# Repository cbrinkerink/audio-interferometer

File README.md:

# audio-interferometer
Using an FPGA to sample audio from multiple digital microphones and perform correlation, then visualise it on a PC. Presently, this repository is a hodgepodge of things including source files, executables, libraries and build scripts. I have tried to stay cross-platform, but everything so far only has been made to compile on OSX.

## Sources used
I have used OpenGL C++ code from the LearnOpenGL tutorial series (specifically, tutorial 4.1 from section 1). I got the serial connection stuff from a question on stackoverflow :)

The Ethernet core is from LiteEth, it is an independently synthesized core using the gen.py script in that codebase.

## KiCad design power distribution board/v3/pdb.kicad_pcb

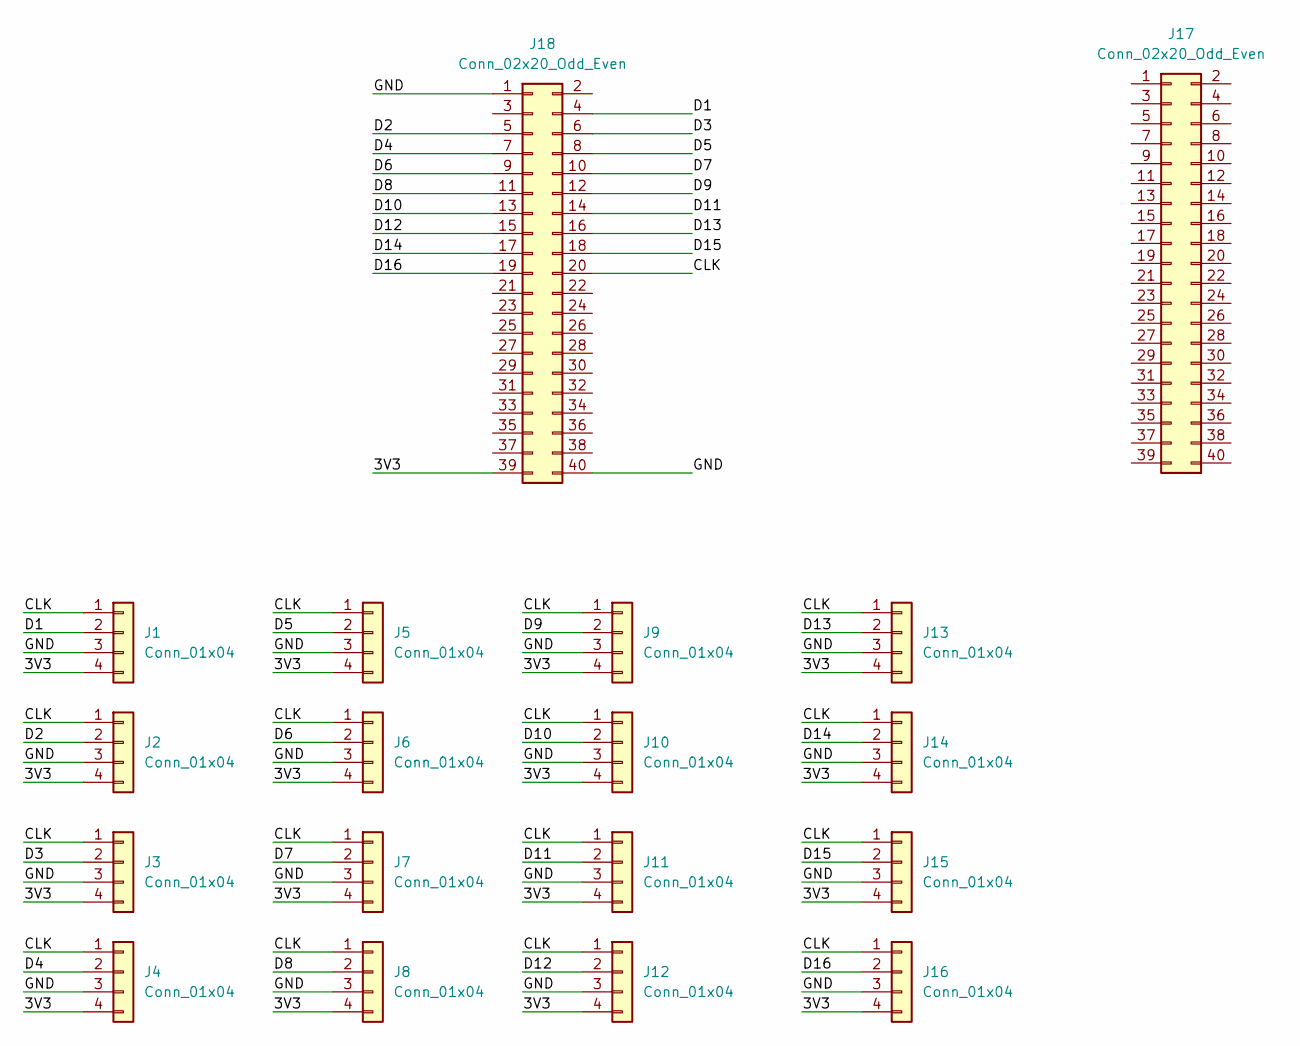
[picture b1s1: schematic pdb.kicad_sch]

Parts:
J1, J2, J3, J4, J5, J6, J7, J8, J9, J10, J11, J12, J13, J14, J15, J16: Conn_01x04; PinHeader_1x04_P2.54mm_Horizontal
J17, J18: Conn_02x20_Odd_Even; PinSocket_2x20_P2.54mm_Vertical

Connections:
/3V3: J1.4, J2.4, J3.4, J4.4, J5.4, J6.4, J7.4, J8.4, J9.4, J10.4, J11.4, J12.4, J13.4, J14.4, J15.4, J16.4, J18.39
/CLK: J1.1, J2.1, J3.1, J4.1, J5.1, J6.1, J7.1, J8.1, J9.1, J10.1, J11.1, J12.1, J13.1, J14.1, J15.1, J16.1, J18.20
/D1: J1.2, J18.4
/D2: J2.2, J18.5
/D3: J3.2, J18.6
/D4: J4.2, J18.7
/D5: J5.2, J18.8
/D6: J6.2, J18.9
/D7: J7.2, J18.10
/D8: J8.2, J18.11
/D9: J9.2, J18.12
/D10: J10.2, J18.13
/D11: J11.2, J18.14
/D12: J12.2, J18.15
/D13: J13.2, J18.16
/D14: J14.2, J18.17
/D15: J15.2, J18.18
/D16: J16.2, J18.19
/GND: J1.3, J2.3, J3.3, J4.3, J5.3, J6.3, J7.3, J8.3, J9.3, J10.3, J11.3, J12.3, J13.3, J14.3, J15.3, J16.3, J18.1, J18.40

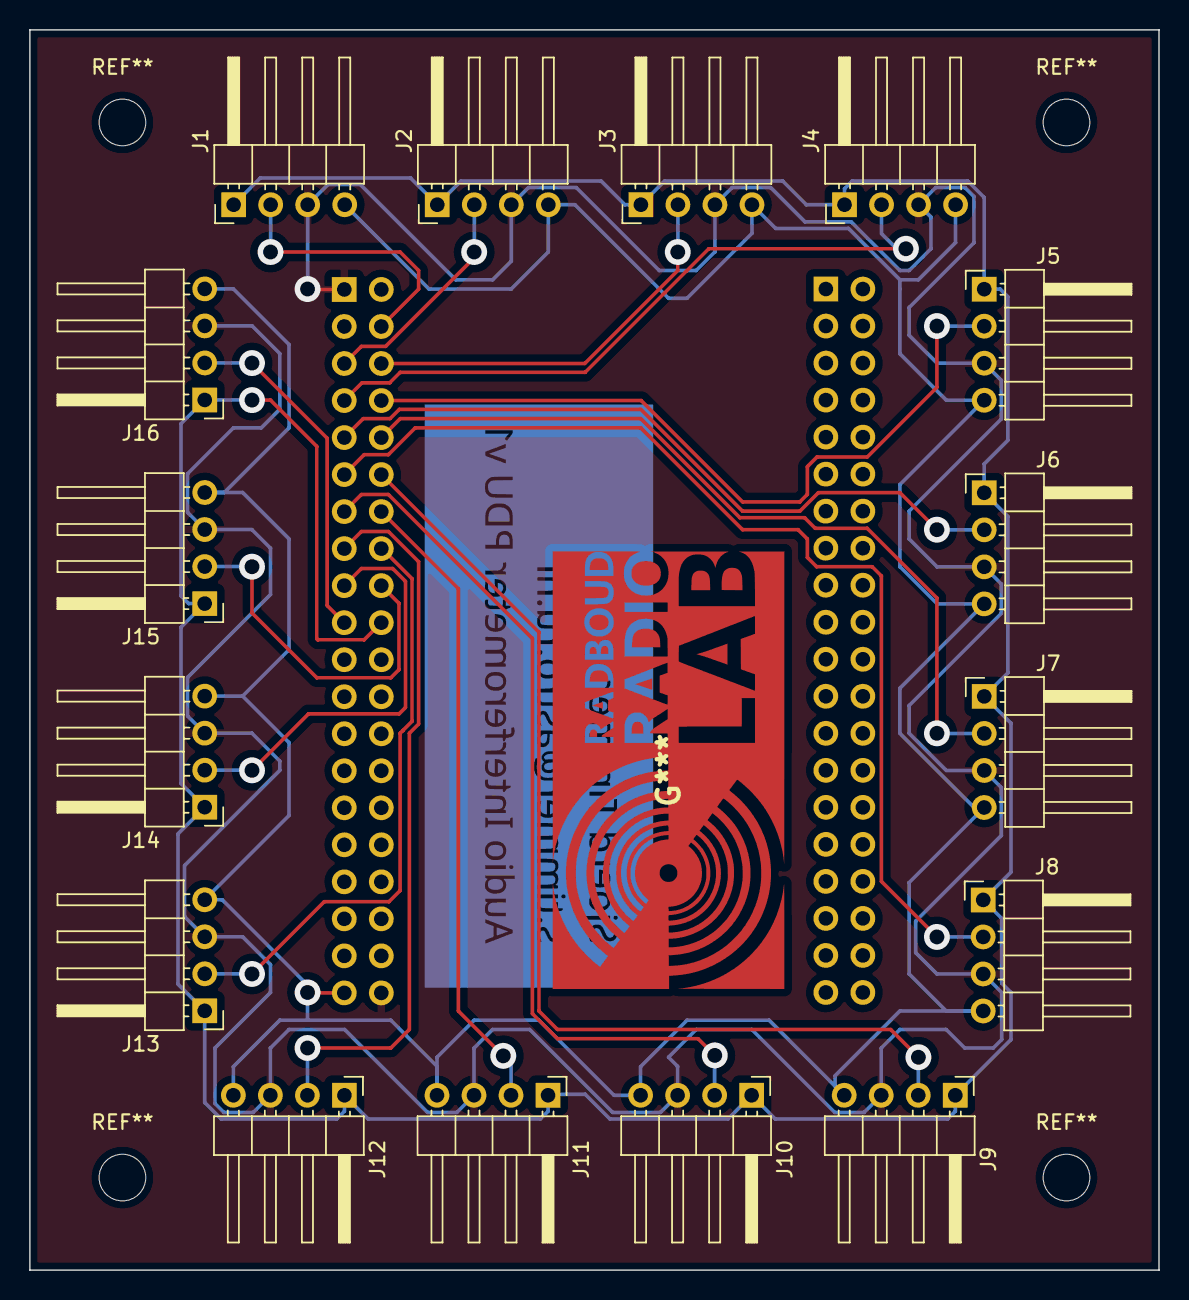
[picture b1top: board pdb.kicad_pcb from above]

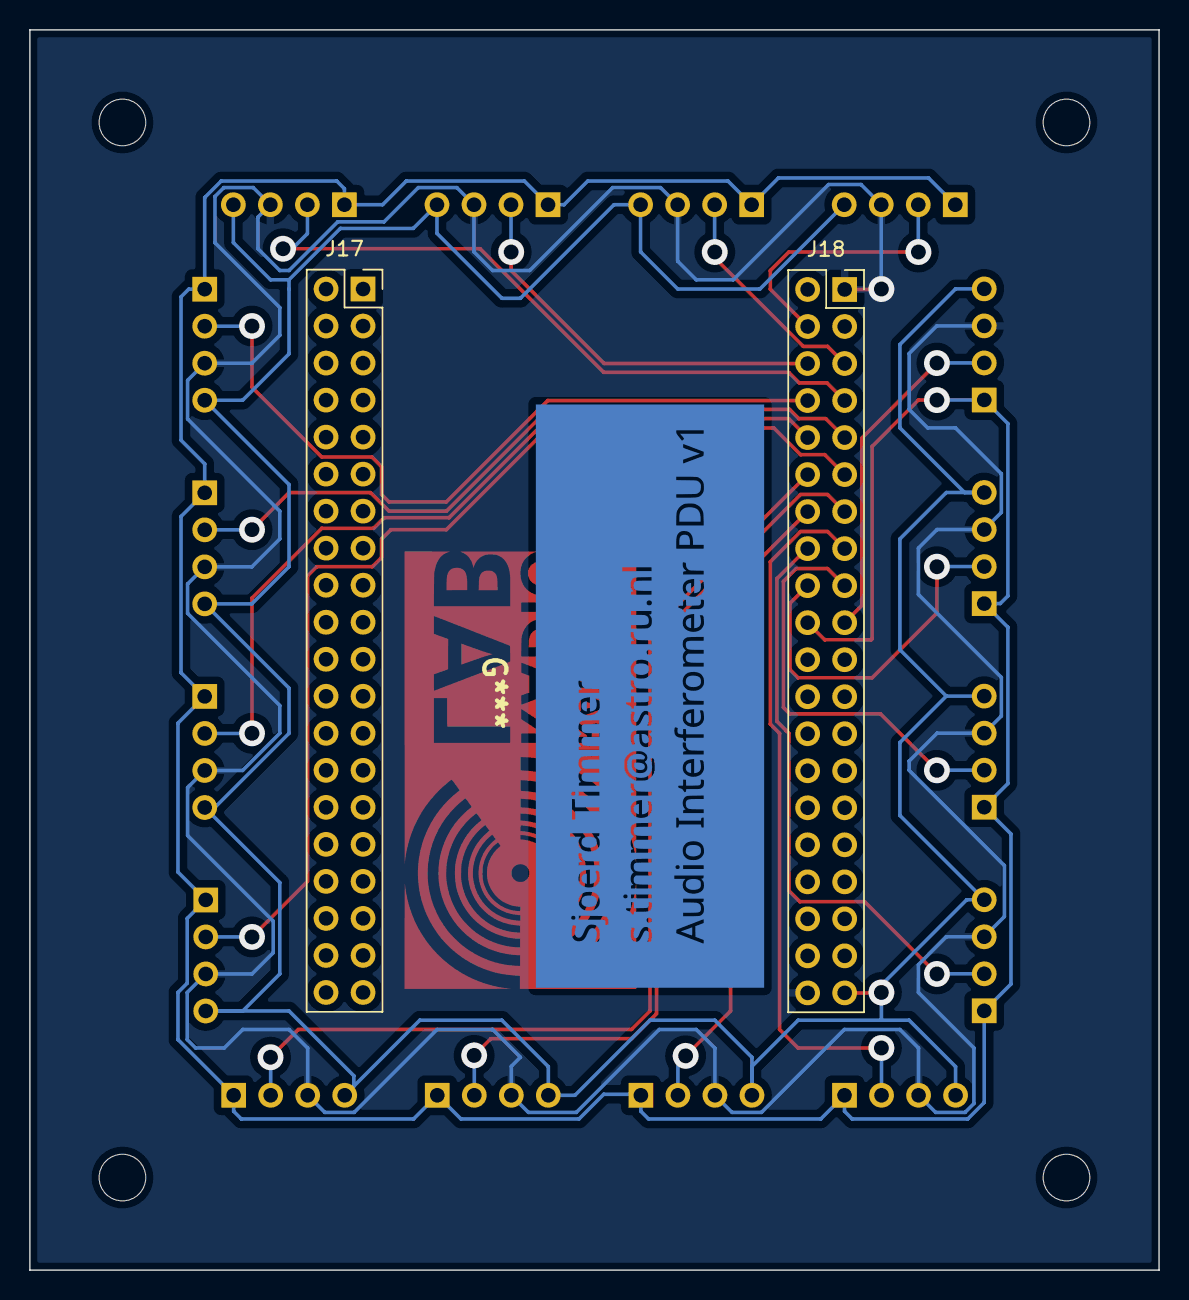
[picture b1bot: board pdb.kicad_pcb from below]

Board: 2 copper layers, 77.5 x 85.1 mm, 18 parts (2 on the bottom side), 19 nets.

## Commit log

2022-07-26 Added FPGA code
2022-07-27 Separate shaders for client
2022-07-27 2D positioning implemented, in-plane only
2022-07-28 Implemented sky-dome direction tracking
2022-07-28 Added display modes (T/P), calibrated lags by eye using a noise source
2022-08-29 First working correlator with ethernet data output
2022-08-29 Bugfixes
2022-09-07 Scalable number of mics, works with 8 mics and 128 lags
2022-09-13 Now works with larger number of lags (256, 512), ethernet packet structure still needs to be updated
2022-09-13 Add preliminary version of power distribution board.
2022-09-14 More versions of power distribution board.
2022-09-14 Tweaks to the layout.
2022-10-05 Added loadable JSON config file
2022-10-05 Updated compile script for JSON use, fragment shader, pin mapping
2022-10-06 Updated verilog code to work with Sjoerd's header board
2022-10-06 Added live init of ethernet link
2022-10-25 Added JSON configurability
2022-11-11 added configurable sky dome radius
